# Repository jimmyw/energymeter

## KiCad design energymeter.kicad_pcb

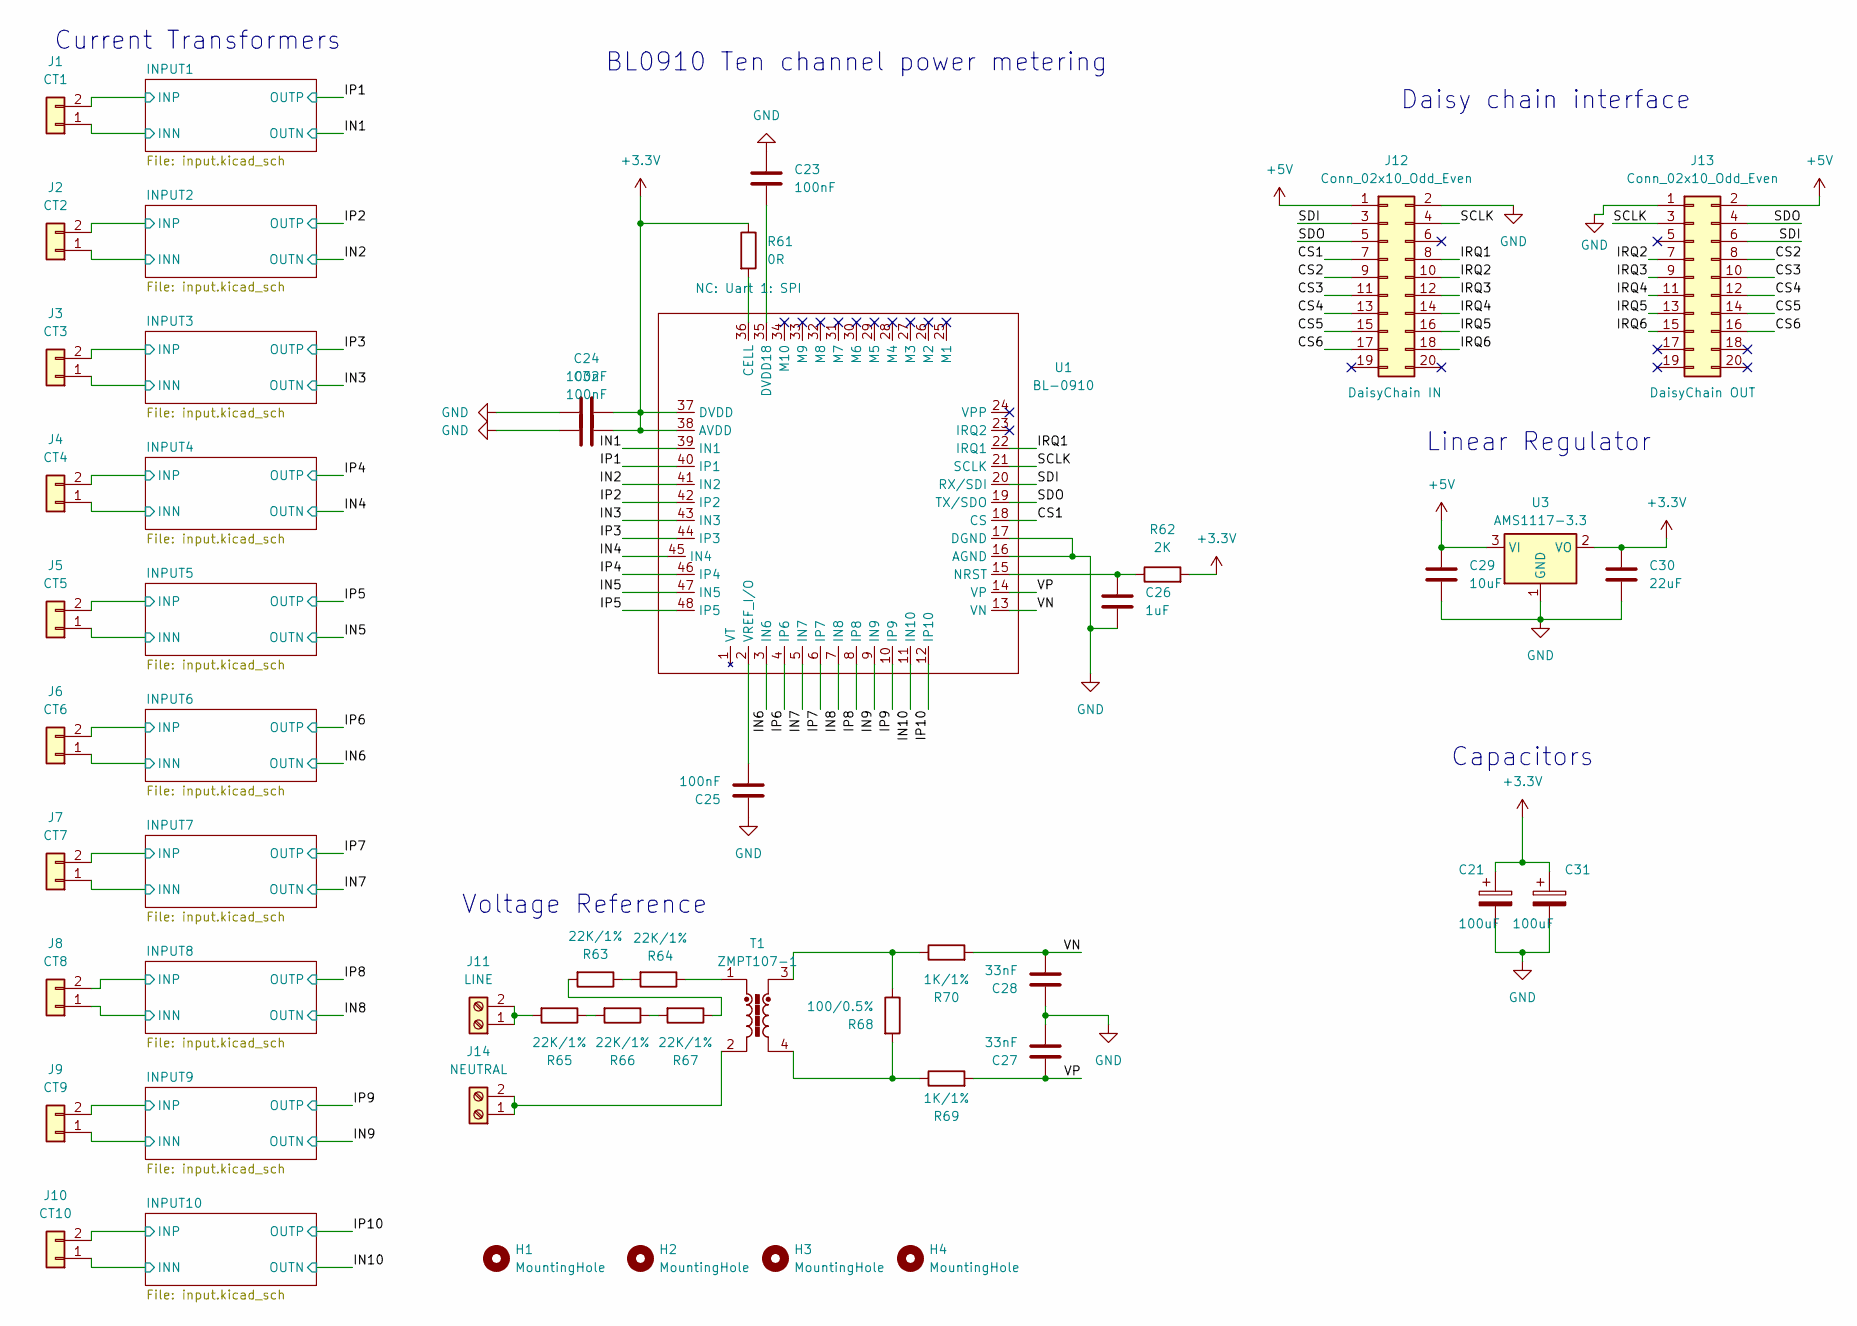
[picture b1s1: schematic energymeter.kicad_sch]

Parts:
C21, C31: 100uF; CP_EIA-3528-21_Kemet-B; LCSC C16133
C23, C24, C25, C32: 100nF; C_0603_1608Metric; LCSC C14858
C26: 1uF; C_0603_1608Metric; LCSC C15849
C27, C28: 33nF; C_0603_1608Metric; LCSC C21117
C29: 10uF; C_0603_1608Metric; LCSC C14858
C30: 22uF; C_0603_1608Metric; LCSC C59461
H1, H2, H3, H4: MountingHole; MountingHole_2.2mm_M2_Pad
J1: CT1; JST_XH_B2B-XH-A_1x02_P2.50mm_Vertical; LCSC C265283
J2: CT2; JST_XH_B2B-XH-A_1x02_P2.50mm_Vertical; LCSC C265283
J3: CT3; JST_XH_B2B-XH-A_1x02_P2.50mm_Vertical; LCSC C265283
J4: CT4; JST_XH_B2B-XH-A_1x02_P2.50mm_Vertical; LCSC C265283
J5: CT5; JST_XH_B2B-XH-A_1x02_P2.50mm_Vertical; LCSC C265283
J6: CT6; JST_XH_B2B-XH-A_1x02_P2.50mm_Vertical; LCSC C265283
J7: CT7; JST_XH_B2B-XH-A_1x02_P2.50mm_Vertical; LCSC C265283
J8: CT8; JST_XH_B2B-XH-A_1x02_P2.50mm_Vertical; LCSC C265283
J9: CT9; JST_XH_B2B-XH-A_1x02_P2.50mm_Vertical; LCSC C265283
J10: CT10; JST_XH_B2B-XH-A_1x02_P2.50mm_Vertical; LCSC C265283
J11: LINE; TerminalBlock_Phoenix_MKDS-1,5-2_1x02_P5.00mm_Horizontal; LCSC C128027
J12: Conn_02x10_Odd_Even; PinHeader_2x10_P2.54mm_Vertical; LCSC C5454488
J13: Conn_02x10_Odd_Even; PinHeader_2x10_P2.54mm_Vertical; LCSC C239361
J14: NEUTRAL; TerminalBlock_Phoenix_MKDS-1,5-2_1x02_P5.00mm_Horizontal; LCSC C128027
R61: 0R; R_0603_1608Metric; LCSC C21189
R62: 2K; R_0603_1608Metric; LCSC C22975
R63, R64, R65, R66, R67: 22K/1%; R_0603_1608Metric; LCSC C31850
R68: 100/0.5%; R_0603_1608Metric; LCSC C22775
R69, R70: 1K/1%; R_0603_1608Metric; LCSC C21190
T1: ZMPT107-1; LCSC C125191
U1: BL-0910; LQFP-48_7x7mm_P0.5mm; LCSC C2841006
U3: AMS1117-3.3; SOT-223-3_TabPin2; LCSC C6186

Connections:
+3.3V: C21.1, C24.2, C30.1, C31.1, C32.2, R61.1, R62.2, U1.37 (DVDD), U1.38 (AVDD), U3.2 (VO)
+5V: C29.1, J12.1, J13.2, U3.3 (VI)
/CS1: J12.7, U1.18 (CS)
/CS2: J12.9, J13.8
/CS3: J12.11, J13.10
/CS4: J12.13, J13.12
/CS5: J12.15, J13.14
/CS6: J12.17, J13.16
/IN1: U1.39 (IN1); also elsewhere on the board
/IN2: U1.41 (IN2); also elsewhere on the board
/IN3: U1.43 (IN3); also elsewhere on the board
/IN4: U1.45 (IN4); also elsewhere on the board
/IN5: U1.47 (IN5); also elsewhere on the board
/IN6: U1.3 (IN6); also elsewhere on the board
/IN7: U1.5 (IN7); also elsewhere on the board
/IN8: U1.7 (IN8); also elsewhere on the board
/IN9: U1.9 (IN9); also elsewhere on the board
/IN10: U1.11 (IN10); also elsewhere on the board
/INPUT1/INN: J1.1; also elsewhere on the board
/INPUT1/INP: J1.2; also elsewhere on the board
/INPUT2/INN: J2.1; also elsewhere on the board
/INPUT2/INP: J2.2; also elsewhere on the board
/INPUT3/INN: J3.1; also elsewhere on the board
/INPUT3/INP: J3.2; also elsewhere on the board
/INPUT4/INN: J4.1; also elsewhere on the board
/INPUT4/INP: J4.2; also elsewhere on the board
/INPUT5/INN: J5.1; also elsewhere on the board
/INPUT5/INP: J5.2; also elsewhere on the board
/INPUT6/INN: J6.1; also elsewhere on the board
/INPUT6/INP: J6.2; also elsewhere on the board
/INPUT7/INN: J7.1; also elsewhere on the board
/INPUT7/INP: J7.2; also elsewhere on the board
/INPUT8/INN: J8.1; also elsewhere on the board
/INPUT8/INP: J8.2; also elsewhere on the board
/INPUT9/INN: J9.1; also elsewhere on the board
/INPUT9/INP: J9.2; also elsewhere on the board
/INPUT10/INN: J10.1; also elsewhere on the board
/INPUT10/INP: J10.2; also elsewhere on the board
/IP1: U1.40 (IP1); also elsewhere on the board
/IP2: U1.42 (IP2); also elsewhere on the board
/IP3: U1.44 (IP3); also elsewhere on the board
/IP4: U1.46 (IP4); also elsewhere on the board
/IP5: U1.48 (IP5); also elsewhere on the board
/IP6: U1.4 (IP6); also elsewhere on the board
/IP7: U1.6 (IP7); also elsewhere on the board
/IP8: U1.8 (IP8); also elsewhere on the board
/IP9: U1.10 (IP9); also elsewhere on the board
/IP10: U1.12 (IP10); also elsewhere on the board
/IRQ1: J12.8, U1.22 (IRQ1)
/IRQ2: J12.10, J13.7
/IRQ3: J12.12, J13.9
/IRQ4: J12.14, J13.11
/IRQ5: J12.16, J13.13
/IRQ6: J12.18, J13.15
/SCLK: J12.4, J13.3, U1.21 (SCLK)
/SDI: J12.3, J13.6, U1.20 (RX/SDI)
/SDO: J12.5, J13.4, U1.19 (TX/SDO)
/VN: C28.2, R70.2, U1.13 (VN)
/VP: C27.1, R69.2, U1.14 (VP)
GND: C21.2, C23.1, C24.1, C25.1, C26.2, C27.2, C28.1, C29.2, C30.2, C31.2, C32.1, J12.2, J13.1, U1.16 (AGND), U1.17 (DGND), U3.1 (GND); also elsewhere on the board
unnamed: J11.1, J11.2, R65.2
unnamed: J14.1, J14.2, T1.2
unnamed: R63.1, R64.2
unnamed: R63.2, R67.1
unnamed: R64.1, T1.1
unnamed: R65.1, R66.2
unnamed: R66.1, R67.2
unnamed: R68.1, R70.1, T1.3
unnamed: R68.2, R69.1, T1.4
unnamed: R61.2, U1.36 (CELL)
unnamed: C23.2, U1.35 (DVDD18)
unnamed: C26.1, R62.1, U1.15 (NRST)
unnamed: C25.2, U1.2 (VREF_I/O)

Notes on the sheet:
Voltage Reference
Capacitors
Daisy chain interface
Linear Regulator
Current Transformers
BL0910 Ten channel power metering

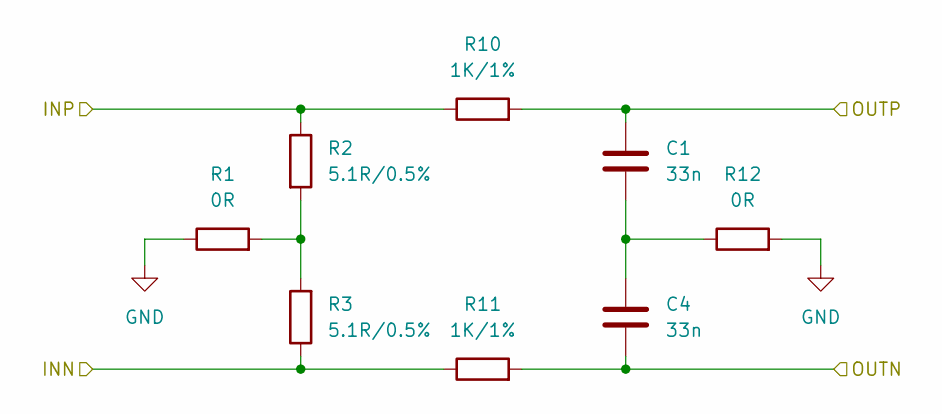
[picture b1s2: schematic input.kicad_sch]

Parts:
C1, C4: 33n; C_0603_1608Metric; LCSC C21117
R1, R12: 0R; R_0603_1608Metric; LCSC C21189
R2, R3: 5.1R/0.5%; R_0603_1608Metric; LCSC C657209
R10, R11: 1K/1%; R_0603_1608Metric; LCSC C21190

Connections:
/IN2: C4.1, R11.2; also elsewhere on the board
/INPUT2/INN: R3.1, R11.1; also elsewhere on the board
/INPUT2/INP: R2.1, R10.1; also elsewhere on the board
/IP2: C1.2, R10.2; also elsewhere on the board
GND: R1.1, R12.2; also elsewhere on the board
unnamed: C1.1, C4.2, R12.1
unnamed: R1.2, R2.2, R3.2

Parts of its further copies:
C2, C3, C5, C6, C7, C8, C9, C10, C11, C12, C13, C14, C15, C16, C17, C18, C19, C20: 33n; C_0603_1608Metric; LCSC C21117
R4, R9, R13, R18, R19, R24, R25, R30, R31, R36, R37, R42, R43, R48, R49, R54, R55, R60: 0R; R_0603_1608Metric; LCSC C21189
R5, R6, R14, R15, R20, R21, R26, R27, R32, R33, R38, R39, R44, R45, R50, R51, R56, R57: 5.1R/0.5%; R_0603_1608Metric; LCSC C657209
R7, R8, R16, R17, R22, R23, R28, R29, R34, R35, R40, R41, R46, R47, R52, R53, R58, R59: 1K/1%; R_0603_1608Metric; LCSC C21190

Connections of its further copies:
/IN1: C3.1, R8.2; also elsewhere on the board
/IN3: C6.1, R17.2; also elsewhere on the board
/IN4: C8.1, R23.2; also elsewhere on the board
/IN5: C10.1, R29.2; also elsewhere on the board
/IN6: C12.1, R35.2; also elsewhere on the board
/IN7: C14.1, R41.2; also elsewhere on the board
/IN8: C16.1, R47.2; also elsewhere on the board
/IN9: C18.1, R53.2; also elsewhere on the board
/IN10: C20.1, R59.2; also elsewhere on the board
/INPUT1/INN: R6.1, R8.1; also elsewhere on the board
/INPUT1/INP: R5.1, R7.1; also elsewhere on the board
/INPUT3/INN: R15.1, R17.1; also elsewhere on the board
/INPUT3/INP: R14.1, R16.1; also elsewhere on the board
/INPUT4/INN: R21.1, R23.1; also elsewhere on the board
/INPUT4/INP: R20.1, R22.1; also elsewhere on the board
/INPUT5/INN: R27.1, R29.1; also elsewhere on the board
/INPUT5/INP: R26.1, R28.1; also elsewhere on the board
/INPUT6/INN: R33.1, R35.1; also elsewhere on the board
/INPUT6/INP: R32.1, R34.1; also elsewhere on the board
/INPUT7/INN: R39.1, R41.1; also elsewhere on the board
/INPUT7/INP: R38.1, R40.1; also elsewhere on the board
/INPUT8/INN: R45.1, R47.1; also elsewhere on the board
/INPUT8/INP: R44.1, R46.1; also elsewhere on the board
/INPUT9/INN: R51.1, R53.1; also elsewhere on the board
/INPUT9/INP: R50.1, R52.1; also elsewhere on the board
/INPUT10/INN: R57.1, R59.1; also elsewhere on the board
/INPUT10/INP: R56.1, R58.1; also elsewhere on the board
/IP1: C2.2, R7.2; also elsewhere on the board
/IP3: C5.2, R16.2; also elsewhere on the board
/IP4: C7.2, R22.2; also elsewhere on the board
/IP5: C9.2, R28.2; also elsewhere on the board
/IP6: C11.2, R34.2; also elsewhere on the board
/IP7: C13.2, R40.2; also elsewhere on the board
/IP8: C15.2, R46.2; also elsewhere on the board
/IP9: C17.2, R52.2; also elsewhere on the board
/IP10: C19.2, R58.2; also elsewhere on the board
GND: R4.1, R9.2, R13.1, R18.2, R19.1, R24.2, R25.1, R30.2, R31.1, R36.2, R37.1, R42.2, R43.1, R48.2, R49.1, R54.2, R55.1, R60.2; also elsewhere on the board
unnamed: C2.1, C3.2, R9.1
unnamed: C5.1, C6.2, R18.1
unnamed: C7.1, C8.2, R24.1
unnamed: C9.1, C10.2, R30.1
unnamed: C11.1, C12.2, R36.1
unnamed: C13.1, C14.2, R42.1
unnamed: C15.1, C16.2, R48.1
unnamed: C17.1, C18.2, R54.1
unnamed: C19.1, C20.2, R60.1
unnamed: R4.2, R5.2, R6.2
unnamed: R13.2, R14.2, R15.2
unnamed: R19.2, R20.2, R21.2
unnamed: R25.2, R26.2, R27.2
unnamed: R31.2, R32.2, R33.2
unnamed: R37.2, R38.2, R39.2
unnamed: R43.2, R44.2, R45.2
unnamed: R49.2, R50.2, R51.2
unnamed: R55.2, R56.2, R57.2

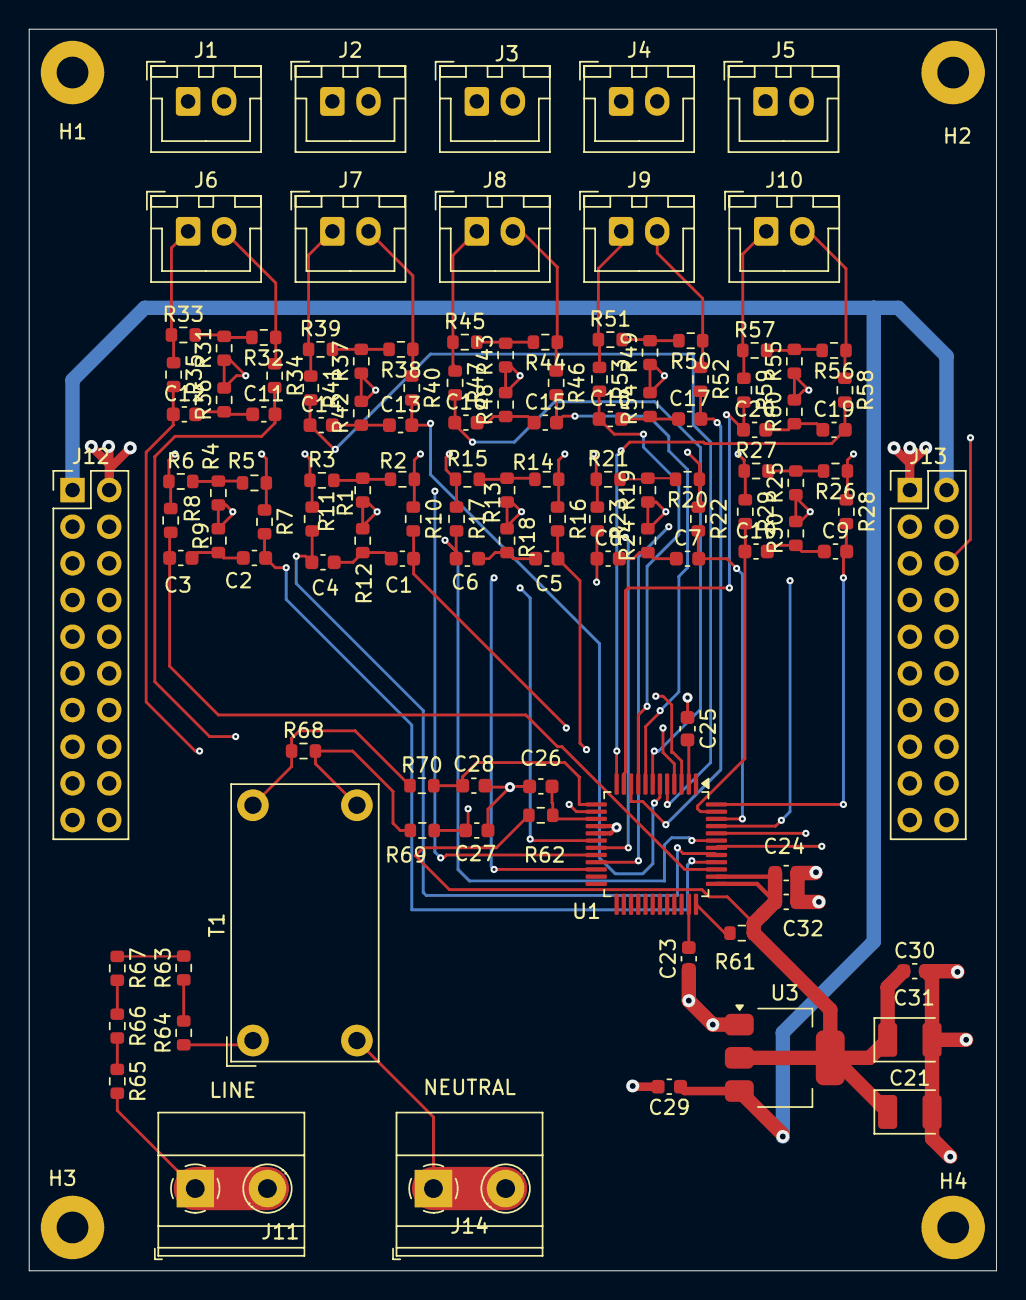
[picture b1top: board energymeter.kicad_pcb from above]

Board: 4 copper layers, 67.0 x 86.0 mm, 122 parts (0 on the bottom side), 93 nets.

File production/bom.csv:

Designator,Footprint,Quantity,Value,LCSC Part #
"C1, C10, C11, C12, C13, C14, C15, C16, C17, C18, C19, C2, C20, C3, C4, C5, C6, C7, C8, C9",0603,20,33n,C21117
"C21, C31",CP_EIA-3528-21_Kemet-B,2,100uF,C16133
"C23, C24, C25, C32",0603,4,100nF,C14858
C26,0603,1,1uF,C15849
"C27, C28",0603,2,33nF,C21117
C29,0603,1,10uF,C14858
C30,0603,1,22uF,C59461
J1,JST_XH_B2B-XH-A_1x02_P2.50mm_Vertical,1,CT1,C265283
J10,JST_XH_B2B-XH-A_1x02_P2.50mm_Vertical,1,CT10,C265283
J11,"TerminalBlock_Phoenix_MKDS-1,5-2_1x02_P5.00mm_Horizontal",1,LINE,C128027
J12,PinHeader_2x10_P2.54mm_Vertical,1,Conn_02x10_Odd_Even,C5454488
J13,PinHeader_2x10_P2.54mm_Vertical,1,Conn_02x10_Odd_Even,C239361
J14,"TerminalBlock_Phoenix_MKDS-1,5-2_1x02_P5.00mm_Horizontal",1,NEUTRAL,C128027
J2,JST_XH_B2B-XH-A_1x02_P2.50mm_Vertical,1,CT2,C265283
J3,JST_XH_B2B-XH-A_1x02_P2.50mm_Vertical,1,CT3,C265283
J4,JST_XH_B2B-XH-A_1x02_P2.50mm_Vertical,1,CT4,C265283
J5,JST_XH_B2B-XH-A_1x02_P2.50mm_Vertical,1,CT5,C265283
J6,JST_XH_B2B-XH-A_1x02_P2.50mm_Vertical,1,CT6,C265283
J7,JST_XH_B2B-XH-A_1x02_P2.50mm_Vertical,1,CT7,C265283
J8,JST_XH_B2B-XH-A_1x02_P2.50mm_Vertical,1,CT8,C265283
J9,JST_XH_B2B-XH-A_1x02_P2.50mm_Vertical,1,CT9,C265283
"R1, R12, R13, R18, R19, R24, R25, R30, R31, R36, R37, R4, R42, R43, R48, R49, R54, R55, R60, R61, R9",0603,21,0R,C21189
"R10, R11, R16, R17, R22, R23, R28, R29, R34, R35, R40, R41, R46, R47, R52, R53, R58, R59, R69, R7, R70, R8",0603,22,1K/1%,C21190
"R14, R15, R2, R20, R21, R26, R27, R3, R32, R33, R38, R39, R44, R45, R5, R50, R51, R56, R57, R6",0603,20,5.1R/0.5%,C657209
R62,0603,1,2K,C22975
"R63, R64, R65, R66, R67",0603,5,22K/1%,C31850
R68,0603,1,100/0.5%,C22775
T1,ZMPT107-1,1,ZMPT107-1,C125191
U1,LQFP-48_7x7mm_P0.5mm,1,BL-0910,C2841006
U3,SOT-223-3_TabPin2,1,AMS1117-3.3,C6186

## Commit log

2024-08-04 Initial add
2024-08-04 Add datasheets
2024-08-04 Add schematic and 3d drawing
2024-08-14 Change connector, assign JLCPCB
2024-08-17 After layout
2024-08-17 add lib paths
2024-08-17 Board cleanup
2024-08-17 First order
2024-09-01 Update picture
2024-09-01 Update schematic
2025-09-19 Add stl files for mount
2025-09-19 Add esphome config
